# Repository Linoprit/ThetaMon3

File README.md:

# ThetaMon3

ThetaMon3 is based on an ESP32 controller, which reads a bunch of sensors and sends the results to a MQTT-Broker, like Mosquitto. I use three probes, together with my Home Assistant installation to control the temperature in remote buildings.

## Features Overview

- Reads DS18B20 sensor array, connected to two channels. In the current configuration, it can read up to five sensors per channel. If you need more, simply increase DS18B20_MAX_DEVICES in Config.h.
- It also reads BME280 values, temp, hummidity and pressure.
- Currently, every channel needs at least one sensor. So a minimum configuration is two DS18B20 sensors and one BME280. 
- Based on a look-up table, placed as file image on the controller, two relays are switched, depending on the given thresholds. Every device works independently.
- Measurements are taken every minute and the average of these measurements are sent to an Mqtt broker every five minutes.
- There is a command-line-interface, you could connect to with a terminal programm, like GTK-Term. So you can have insight, what is going on in your setup and you can change several settings with it.
- Also, there are Mqtt-channels for remote accessing the device, or read loggings.

Why two OneWire-channels?<br>
I simply had the problem that in the workshop the location of the probe was in the middle of the sensor chain. Unfortunately, it was not possible to place it at one end or the other of the sensor chain.

## What's it all about? 

To understand what ThetaMon does and what it is meant for, we take a look at where the idea comes from.

My wife owns really a lot of pot-plants. These must be kept in a warmer place during the winter time, so we bring them into the garages. Unfortunately, on some days the outside temperatures could drop so low, that even in the garage the plants will die. Of course you use an electric heater, but the control of such devices is not particularly precise.
So the idea came up to build a system, that measures at different places in the room, to bring more insight how the heat is distributed and which places are save. Above that, to provide a finer regulation of the heating.

I put together the first version of ThetaMon, based on STM32F103 controllers, it consisted of two satellites and a base-station. The communication was done with NRF24 radios, which are long range capable (more or less...). The base-station was connected to an orange-pi which ran an apache webserver installation and hosted a page to show the graphs of all sensors for the last 24 hours. One very crucial point was, that the satellites work independently. If the connection to the base broke, they must have benn capable to do the regulation. This means, that every node in the system has to keep a table with all relevant temperature-thresholds.

This system ran fine for some years, but I wanted more flexibility and insight, if things went wrong. Sometimes temperature sensors failed, due to connector problems, or the NRF24 modules failed.
ThetaMon2 took a very long time to develop, and it became very complex. For example I needed an EEPROM with some kind of file-system to store the sensor tables. The html-generation was done by own code on the used Banana-Pi. Finaly it worked and it was used for one year.

In winter 2023 I took the time to try, if ESP32 with external antenna could keep a stable connection to the Wlan. And yes, it did! Also I looked for some different possibility to do the development and found, that PlatformIO is so much powerfull. Then, a colleague showed me what he does with home automation and I came up to use Home Assistant as dashboard solution.
ThetaMon3 took only a half year of development, not only because large parts of code from TM2 have been overtaken, it turned out that PlatformIO absolutely speeds up things.

## Getting started

Refer to: [SettingUpThetaMonProbe](https://github.com/Linoprit/ThetaMon3/blob/main/Doc/SettingUpThetaMonProbe.pdf).<br>
You need a working Visual Studio Code, together with PlatformIO. 

For a complete command-reference see [CommandLineReference](https://github.com/Linoprit/ThetaMon3/blob/main/Doc/CommandLineReference.pdf).

## Integrating to Home Assistant

The probes data is transmitted via mqtt, so you could integrate it whereever you want.
Because I use HA, I describe the integration for it. 

The name of your location (spot), where the probe is placed is defined in „MqttConfig.txt“, that resides on your ESP. Every sensor has a shortname, defined in „ID_Table_U64.txt“. These two names result in a mqtt publishing, in the form \<Location>/sens/\<Sensor-Shortname>. Your Home Automation system has to subscribe every sensor. The sensor data is transmitted in Json-format, i.e. "{"HUMID":51.21}"

Your Mosquitto installation and setup should have been done in the last step. You could use Home Assistants Mosquitto plugin.<br>
Go to the file /homeassistant/configuration.yaml, use the text-editor-plugin. 
Create a new section 
```
mqtt:
    sensor:
```
Then for every sensor enter a block like this:
```
    - name: "<Location> <Sensor-Shortname>"
      unique_id: <Location><Sensor-Shortname>
      state_class: "measurement"
      state_topic: "<Location>/sens/<Sensor-Shortname>"
      unit_of_measurement: "°C"
      expire_after: 480
      value_template: "{{ value_json.TEMP }}"
```
### Unit and value_template for other sensors:

Pressure:
```
      unit_of_measurement: "hPa"
      value_template: "{{ value_json.PRESS }}"
```

Hummidity:
```
      unit_of_measurement: "%"
      value_template: "{{ value_json.HUMID }}"
```

Relay:
```
      unit_of_measurement: "0/1"
      value_template: "{{ value_json.RELAY }}"
```

Example configuration:
```
# -- ESP32 Sensors --
mqtt:
    sensor:    
    - name: "Lager Temperatur"
      unique_id: LagerTmp
      state_class: "measurement"
      state_topic: "Lager/sens/LagerTmp"
      unit_of_measurement: "°C"
      expire_after: 480
      value_template: "{{ value_json.TEMP }}"
    - name: "Lager Luftdruck"
      unique_id: LagerPrs
      state_class: "measurement"
      state_topic: "Lager/sens/LagerPrs"
      unit_of_measurement: "hPa"
      expire_after: 480
      value_template: "{{ value_json.PRESS }}"
    - name: "Lager Luftfeuchte"
      unique_id: LagerHum
      state_topic: "Lager/sens/LagerHum"
      state_class: "measurement"
      unit_of_measurement: "%"
      expire_after: 480
      value_template: "{{ value_json.HUMID }}"
    - name: "Lager  Relay 1"
      unique_id: LagerRl1
      state_topic: "Lager/sens/LagerRl1"
      state_class: "measurement"
      unit_of_measurement: "0/1"
      expire_after: 480
      value_template: "{{ value_json.RELAY }}"
    - name: "Lager  Relay 2"
      unique_id: LagerRl2
      state_topic: "Lager/sens/LagerRl2"
      state_class: "measurement"
      unit_of_measurement: "0/1"
      expire_after: 480
      value_template: "{{ value_json.RELAY }}"
```

## Listen to the probes logging
Every probe publishes it's logging. It can be monitored with
```
mosquitto_sub -u mosquitto -P public -h <server-ip> -t <Location>/log
```

## Commands from remote
Via Mosquitto, commands can be sent to your probe with
```
mosquitto_pub -t '<Location>/cmd' -m '<Command>'
```
Best practise is to have a second terminal open with a running log-subscription.

## ToDo
- Explain how TM3 works. Measurement_Pivot, CommLine-Interface...?
- Discussion, if digital input / output channels are needed.
- Make Mqtt-credentials changeable, append them to MqttConfig.
- Move all Mqtt related commands in a structure and apply the "hasChanged" mechanism, used in sensor-configuration.

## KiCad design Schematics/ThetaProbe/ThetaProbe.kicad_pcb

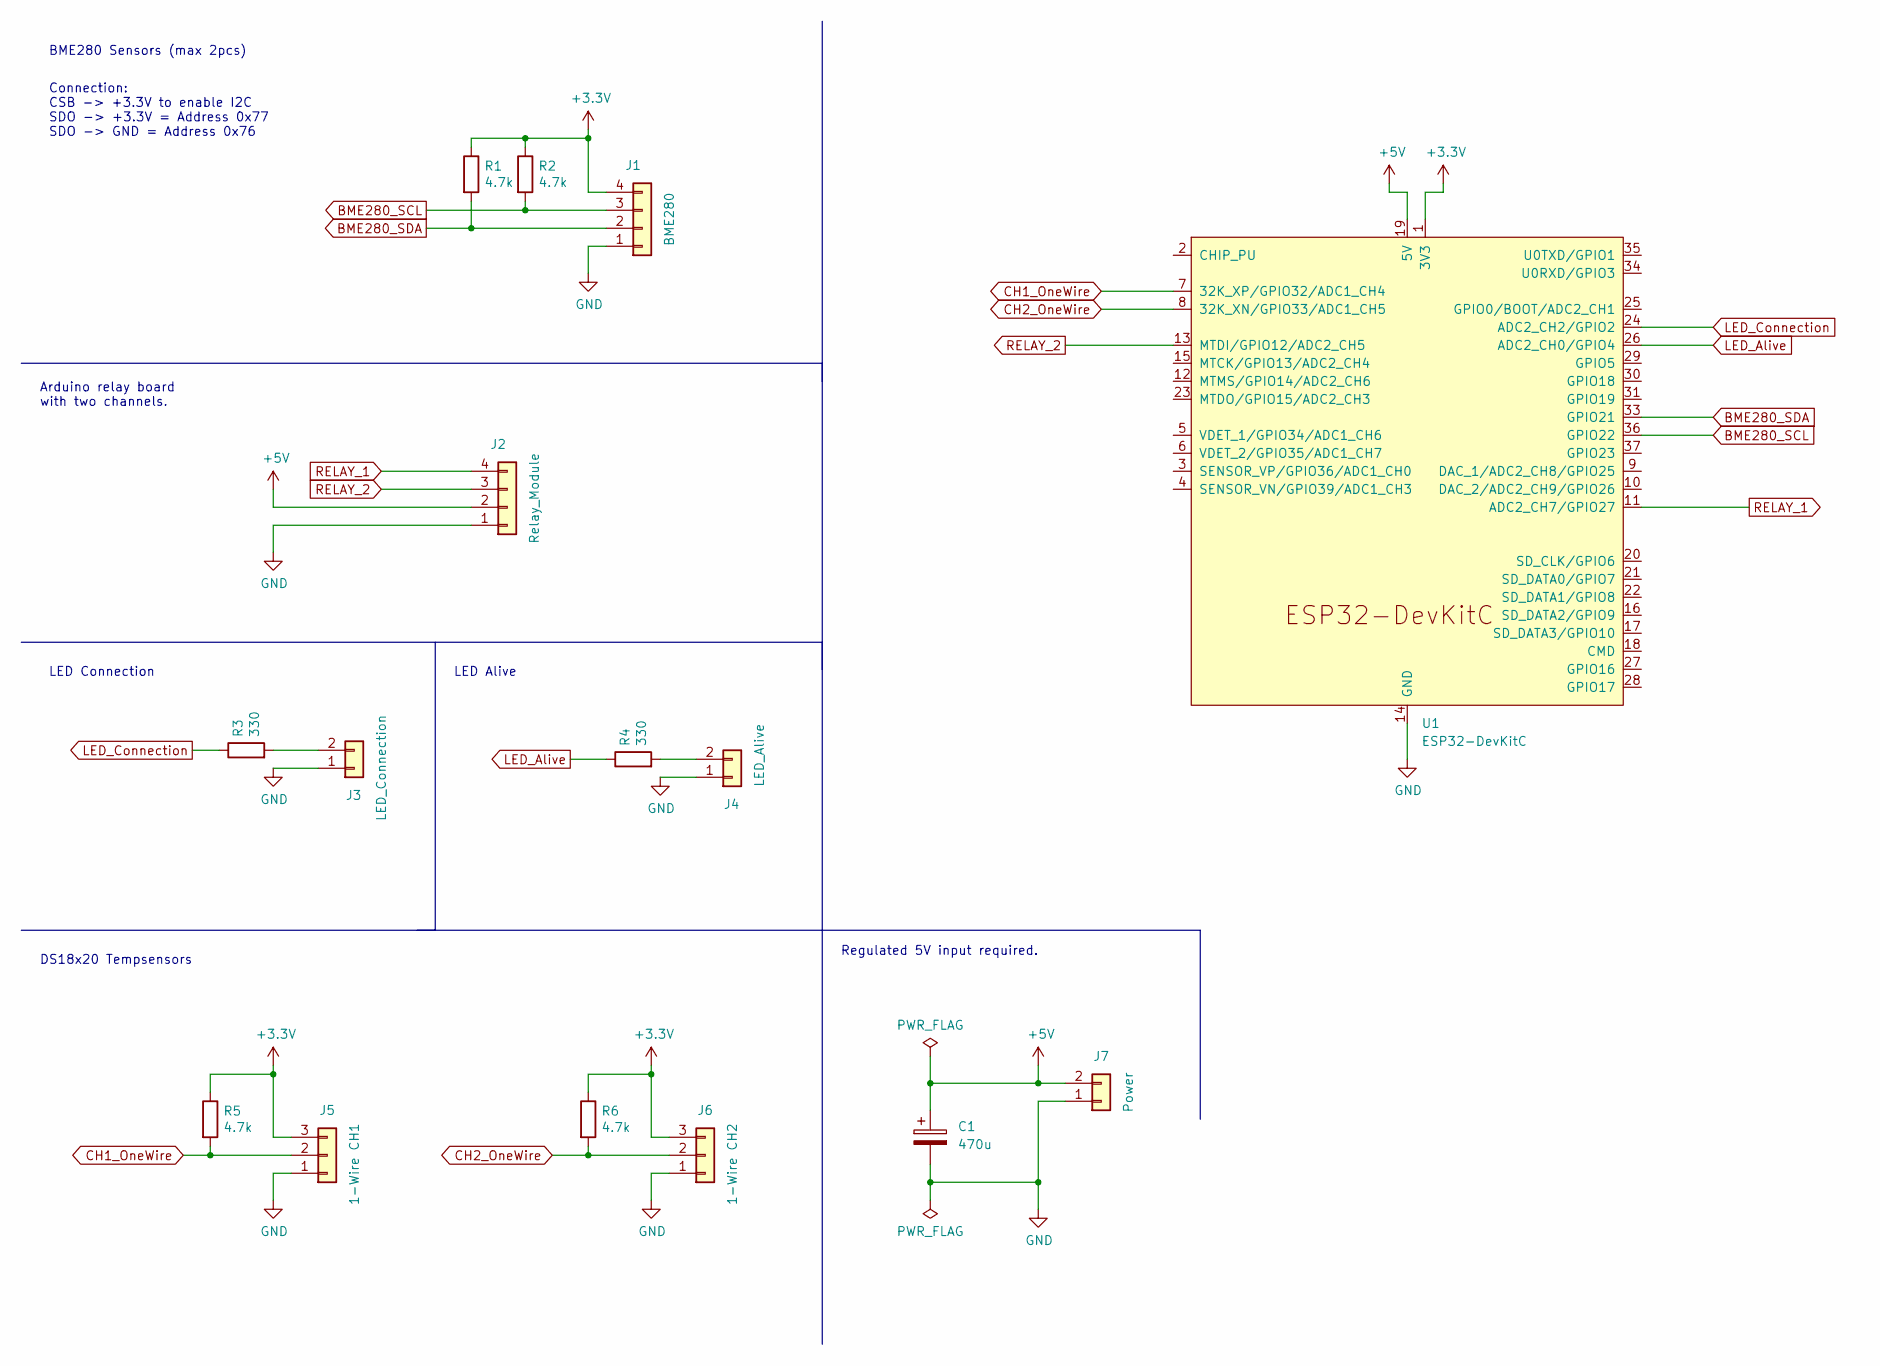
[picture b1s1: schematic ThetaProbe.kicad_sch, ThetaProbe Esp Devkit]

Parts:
C1: 470u; CP_Axial_L11.0mm_D8.0mm_P15.00mm_Horizontal
J1: BME280; Molex_KK-254_AE-6410-04A_1x04_P2.54mm_Vertical
J2: Relay_Module; Molex_KK-254_AE-6410-04A_1x04_P2.54mm_Vertical
J3: LED_Connection; Molex_KK-254_AE-6410-02A_1x02_P2.54mm_Vertical
J4: LED_Alive; Molex_KK-254_AE-6410-02A_1x02_P2.54mm_Vertical
J5: 1-Wire CH1; Molex_KK-254_AE-6410-03A_1x03_P2.54mm_Vertical
J6: 1-Wire CH2; Molex_KK-254_AE-6410-03A_1x03_P2.54mm_Vertical
J7: Power; Molex_KK-254_AE-6410-02A_1x02_P2.54mm_Vertical
R1, R2, R5, R6: 4.7k; R_Axial_DIN0207_L6.3mm_D2.5mm_P7.62mm_Horizontal
R3, R4: 330; R_Axial_DIN0207_L6.3mm_D2.5mm_P7.62mm_Horizontal
U1: ESP32-DevKitC

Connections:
+3V3: J1.4, J5.3, J6.3, R1.1, R2.1, R5.1, R6.1, U1.1 (3V3)
+5V: C1.1, J2.2, J7.2, U1.19 (5V)
BME280_SCL: J1.3, R2.2, U1.36 (GPIO22)
BME280_SDA: J1.2, R1.2, U1.33 (GPIO21)
CH1_OneWire: J5.2, R5.2, U1.7 (32K_XP/GPIO32/ADC1_CH4)
CH2_OneWire: J6.2, R6.2, U1.8 (32K_XN/GPIO33/ADC1_CH5)
GND: C1.2, J1.1, J2.1, J3.1, J4.1, J5.1, J6.1, J7.1, U1.14 (GND), U1.32 (GND), U1.38 (GND)
LED_Alive: R4.1, U1.26 (ADC2_CH0/GPIO4)
LED_Connection: R3.1, U1.24 (ADC2_CH2/GPIO2)
unnamed: J3.2, R3.2
unnamed: J4.2, R4.2
RELAY_1: J2.4, U1.11 (ADC2_CH7/GPIO27)
RELAY_2: J2.3, U1.13 (MTDI/GPIO12/ADC2_CH5)

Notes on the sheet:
BME280 Sensors (max 2pcs)
DS18x20 Tempsensors
Connection: CSB -> +3.3V to enable I2C SDO -> +3.3V = Address 0x77 SDO -> GND = Address 0x76
LED Alive
LED Connection
Arduino relay board with two channels.
Regulated 5V input required.

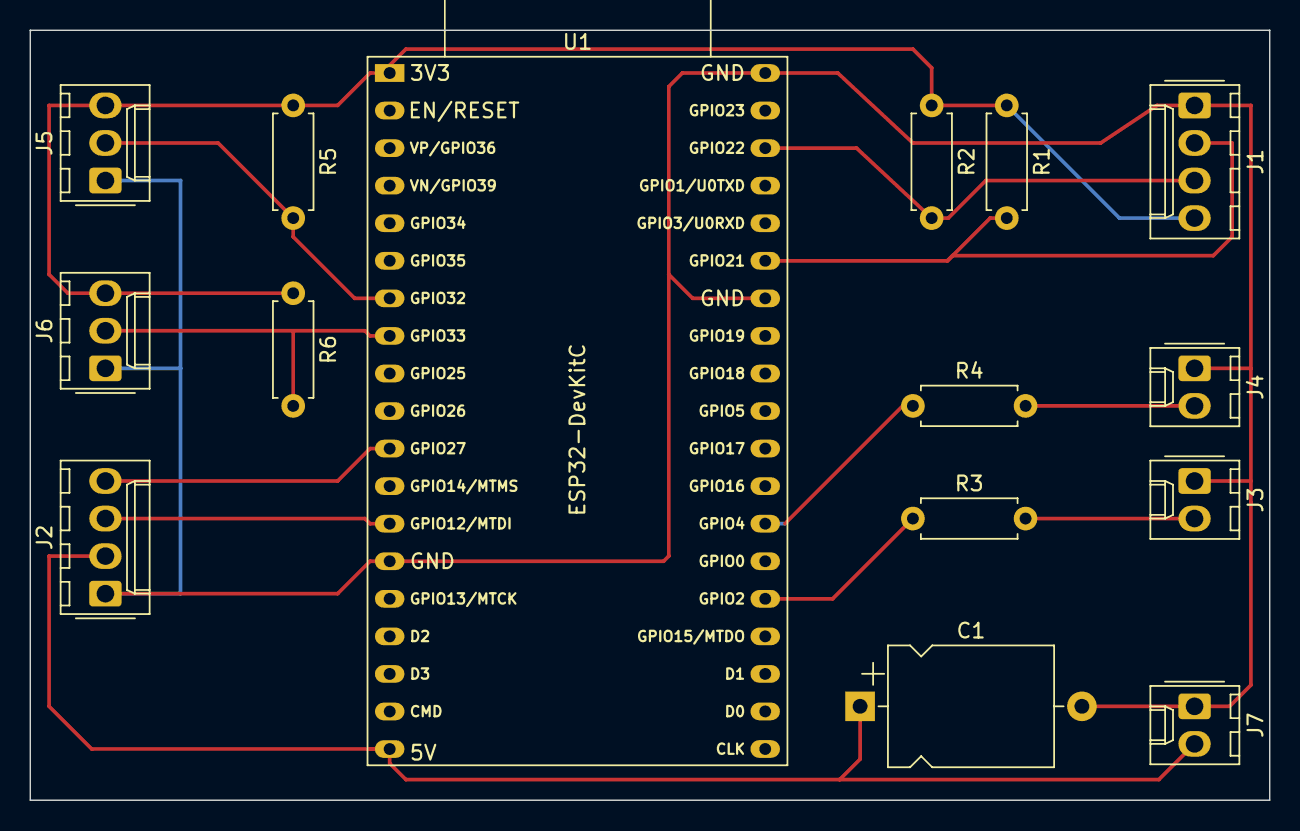
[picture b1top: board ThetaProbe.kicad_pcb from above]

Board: 2 copper layers, 83.8 x 52.1 mm, 15 parts (0 on the bottom side), 13 nets.

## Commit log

2024-01-05 MeasurementPivot with tests done.
2024-01-07 Crc calculation for commandline added
2024-01-20 Measuring cycle with ds1820 works
2024-01-20 Bme280 is working now.
2024-01-21 Old TableIdTool recycled.
2024-01-28 read and write SensIdTable works
2024-02-11 Mqtt publishing of sensor data done
2024-02-12 MqttPublishing works, MqLog works also.
2024-02-15 GPIO Leds and Relays working
2024-02-17 Everything works so far.
2024-02-18 Everything works (so far).
2024-03-17 starting with transfering onewire from old stm32 version.
2024-03-17 commit from local
2024-03-25 OneWire lib for two lines
2024-03-27 Some beautifying
2024-03-29 local changes
2024-03-29 Final version with 5V push-pull schematic.
    Still problems with reading out some sensors. It's no timing issue, and
    no electrical issue. Sensors broken?
2024-03-29 Switching to 3.3V OneWire
2024-03-29 After testing, nothing really changed.
2024-04-05 Beginning with Python Mqtt-Daemon
2024-04-05 Debug LED added.
2024-05-18 OpenHab Test added
2024-05-27 Mqtt for HomeAssistant
2024-08-25 Last tweaks
2024-08-30 Begun documentation
2024-08-30 test md with image
2024-08-30 test md
2024-08-30 Documentation work in progress.
2024-08-30 Rudimentary documentation done.
2024-08-30 CommLine-Ref still missing.
2024-08-30 Command line reference added.
2024-08-30 Sync...
2024-08-30 Now is command line ref added.
2024-08-30 Link updated.
2024-08-30 Some tweaks done.
2024-08-30 Some more tweaks.
2024-09-08 Fixed problem with resolution setting on DS18B20.
2024-10-06 Some last tweaks done.
